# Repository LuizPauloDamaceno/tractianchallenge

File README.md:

# Tractian Challenge for R&D

Tractian's Challenge for Hardware R&D - Final resources and resolution

Project directory:
| Folder | Content | 
|------|------|
| arduino_programs | Contains main programs that i've used to test in my arduino boards. |
| eagle_schematics_and_pcb | Base project that can be used for Tx / Rx hardware |
| python_scripts | Base scripts used to send, fragment, reconstruct and append data |
| real_implementations_data | Source data that was transfered through bridges or Wireless and its results at its real uses (phase analysis in time domain) |
| initial_planning | manual drawings of how things can be |

Observations: 

	- The data file contains about 36000 points of 13 byte string (coming from a time interval counter that puts data into this file every second with picossecond (pS) resolution).
	- The benchmarks for base tests showed the following results:

		- Bridge mode (case 1): about 15 min to transfer entire data;
		- Wireless mode (case 2): about 2 hours to transfer entire data.

Initially, i've decided to make the communication bridge (Tx and Rx systems) most modular as possible. So, in this project we have four parts:

	1 - The data what's going to be sent;
	2 - The board who talks (or not) with some serial wireless transceiver;
	3 - The board or client with also some wireless transceiver;
	4 - The incoming data reconstruction program (embedded at the board in step 3 or not).

We have the follwing implementations for proof of concept:

| Case | Transmitting device | Fragmentation method | Receiving device | Reconstruction method | 
|------|------|------|------|------|
| 1, wired | Arduino Mega | Python readlines of original file + SerialBuffer getting SoftwareSerial data | Arduino Mega | Python appending incoming serial lines to a file |
| 2, wireless | Arduino Uno | Python readlines of original file + SerialBuffer getting SoftwareSerial data | ESP8266 configured as client in home wireless networking, serving a TCP stream at its port 333 | Python appending incoming socket client data lines to a file |

For case 2, 80m air gap was reached (with few obstachles in the middlepath) by following  diagram:

| Arduino Uno + ESP8266 | ------ air gap (80m) -----> | Wi-Fi router (OpenWrt, TxPower @23dBm) | -----------> | personal computer connected by USB dongle (also 80m from the router) accessing ESP8266 TCP server in LAN |

For the schematics, I've decided to keep uControllers pins unused open. This makes path for futher implementations, depending of the modem model that we want to use. 

Also, make note that i've choosen Atmega328 uController, that can be replaced for few uControllers of different Atmel's family. Of course, few layout settings should be replanned if other uControllers want to be implemmented. 

Concerning the voltage regulating parts, i've choose a regulator that can step up voltage from an ordinary 18650 Li-Ion battery with some quality. We have many decoupling capacitors here because of current peaks that regulator may have an slow response and this may result in loss of packet transfer or even hardware bug. 

If is the case of integrating ESP8266 board (or any other radio, such as LoRa ones) into main uController's board, few R.F. cares should be taken into account, such as:

	1 - Never put an transmitter (of whatever frequency) near to main uControlers XTAL, or injection locking may occur, degrading overall system performance or stopping system working;
	2 - Striplines for antennas are the best design form: it's compact and we can dimension it in accordance with frequency wavelenght, for this, higher Transmitting and Receiving frequency may be optimal, since lower freququencies will have big transmission lines;
	3 - Decoupling inductors and capacitors for power amplifiers are good idea for removing transmission noise from the overall system;
	4 - Avoid 90º lines at PCB, this may irradiate signals and degrade system's performance;

The main schematic and board relies in an external radio device operating by a serial port that is virtual. Any radio device that operates by sending serial data through air will work with this project. Other implementations such as i2c or SPI radios may work with few changings in the project.

The project as it is has the same board for RX and TX, relying on the first concept of "Case 1". Now, some pin descriptions:
| Pin | Description |
|------|------|
| +VBAT / -VBAT | 18650 Battery connections pins |
| MVCC / MGND | Main VCC / GND connections - If wanted, works without battery or with external power supply. This also makes the possibility of use battery as back-up |
| RF_VCC / RF_GND | External module feeding, relying on 5V power supply for hungry modules |
| RF_TX / RF_RX | External module data feeding / receiving, this is the communication link |

As you can see until here, the project was designed to use an uController as bridge, wich connects the data to the transmission <-> or transmission with the data storage.
Faster radios or even better uControllers certainly will improve system's overall speed (such as few LoRa modems (like SX12xx series) with STM32 uController. Maybe is also interesting future tests with BLE (Bluetooth Low Energy) devices. 

The main reason of componnents / modules choice is based on what I had to test and proof the work of basic system in my own lab. As you can see in the .ino or .py programs, the codes are completely portable to any wanted platform. Such as STM32, or even an mBed board, for example. 

Is also possible to observe that even with ESP solution, if speed isn't a problem, interactive plots may be done with a simple code. If you also want to view few videos of the real implementations working, check here: https://tinyurl.com/mwtjrbfp

References:

	https://room-15.github.io/blog/2015/03/26/esp8266-at-command-reference/
	https://docs.espressif.com/projects/esp-at/en/latest/esp32/AT_Command_Set/Wi-Fi_AT_Commands.html
	https://www.electronicshub.org/esp8266-at-commands/
	https://www.espressif.com/sites/default/files/documentation/4b-esp8266_at_command_examples_en.pdf
	https://github.com/beegee-tokyo/SX126x-Arduino#explanation-for-txco-and-antenna-control

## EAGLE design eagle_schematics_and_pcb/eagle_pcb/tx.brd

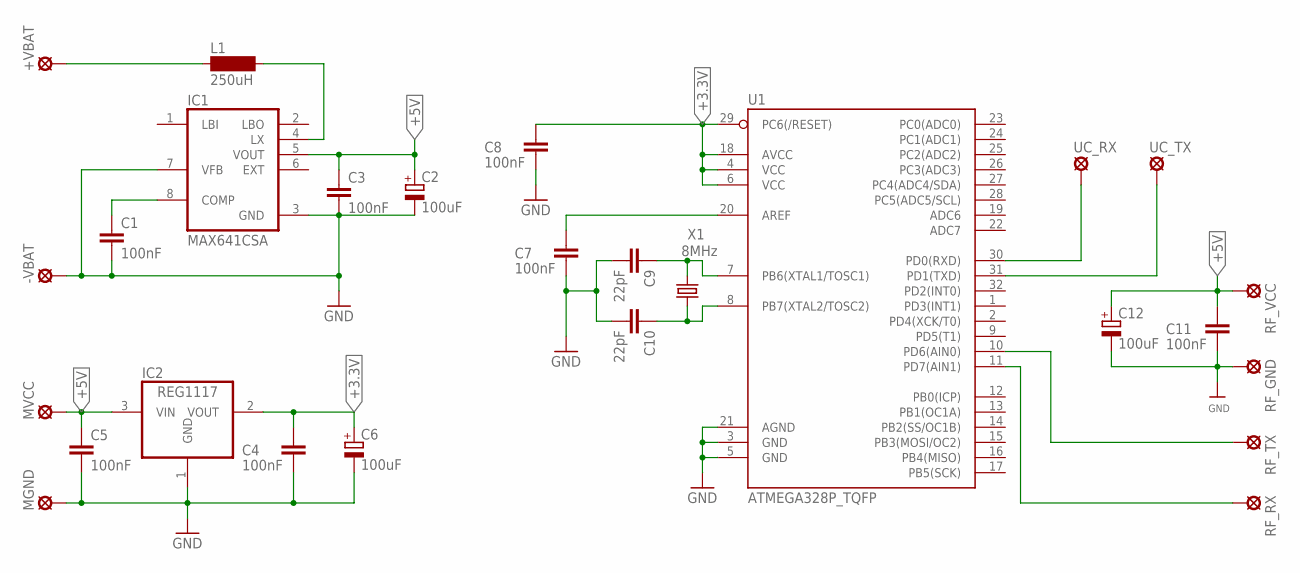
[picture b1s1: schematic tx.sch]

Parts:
+VBAT: SE14
-VBAT: SE14
C1, C3, C4, C5, C7, C8, C11: 100nF; C1206
C2, C6, C12: 100uF; 140CLH-0810
C9, C10: 22pF; 0603
IC1: MAX641CSA; SO08
IC2: REG1117; SOT223
L1: 250uH; MS50
MGND: SE14
MVCC: SE14
RF_GND: SE14
RF_RX: SE14
RF_TX: SE14
RF_VCC: SE14
U1: ATMEGA328P_TQFP; TQFP32-08
UC_RX: SE14
UC_TX: SE14
X1: 8MHz; CSM-7X-DU

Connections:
+3.3V: C4.1, C6.+, C8.1, IC2.2 (VOUT), U1.4 (VCC), U1.6 (VCC), U1.18 (AVCC), U1.29 (PC6(/RESET))
+5V: C2.+, C3.1, C5.1, C11.1, C12.+, IC1.5 (VOUT), IC2.3 (VIN), MVCC.MP, RF_VCC.MP
GND: -VBAT.MP, C1.2, C2.-, C3.2, C4.2, C5.2, C6.-, C7.2, C8.2, C9.2, C10.2, C11.2, C12.-, IC1.3 (GND), IC1.7 (VFB), IC2.1 (GND), MGND.MP, RF_GND.MP, U1.3 (GND), U1.5 (GND), U1.21 (AGND)
unnamed: IC1.4 (LX), L1.2
unnamed: C1.1, IC1.8 (COMP)
unnamed: C7.1, U1.20 (AREF)
unnamed: +VBAT.MP, L1.1
unnamed: RF_RX.MP, U1.11 (PD7(AIN1))
unnamed: C9.1, U1.7 (PB6(XTAL1/TOSC1)), X1.1
unnamed: C10.1, U1.8 (PB7(XTAL2/TOSC2)), X1.2
unnamed: RF_TX.MP, U1.10 (PD6(AIN0))
unnamed: U1.30 (PD0(RXD)), UC_RX.MP
unnamed: U1.31 (PD1(TXD)), UC_TX.MP

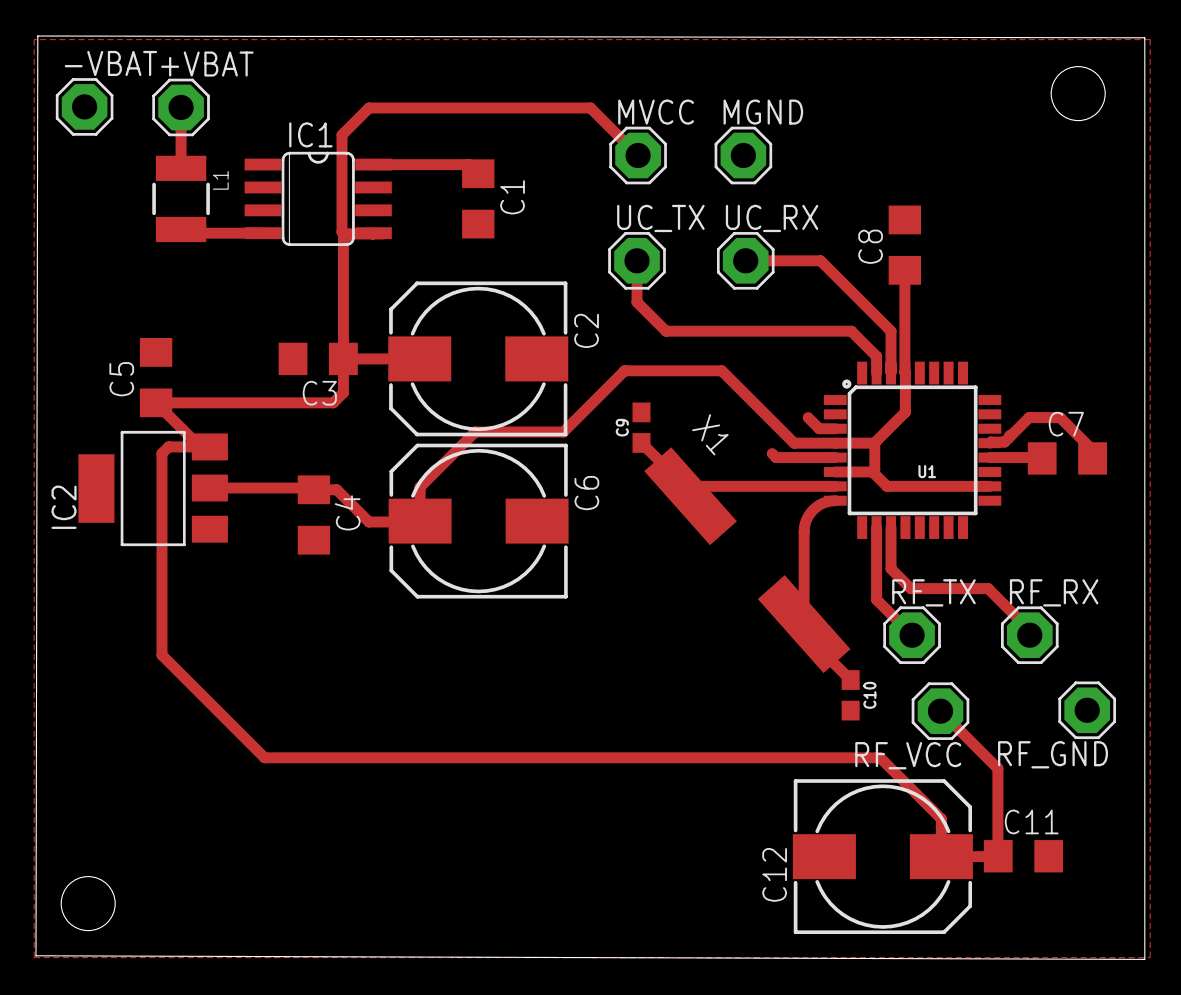
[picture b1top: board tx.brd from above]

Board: 2 copper layers, 61.6 x 51.3 mm, 27 parts (0 on the bottom side), 13 nets.

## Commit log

2022-07-26 Update README
    remembering how to commit and edit things here.
2022-07-26 Add project informations
2022-07-26 fix README typo
2022-07-26 Update some informations
    add details
2022-07-26 add main files
    entire project is here.
2022-07-26 add extra info
2022-07-26 add initial plan that was missing

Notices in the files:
parts and their libraries:
SparkFun-Capacitors: Licensing: Creative Commons ShareAlike 4.0 International - https://creativecommons.org/licenses/by-sa/4.0
